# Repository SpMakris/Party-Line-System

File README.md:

# Party-Line-System
Party Line circuit implementation

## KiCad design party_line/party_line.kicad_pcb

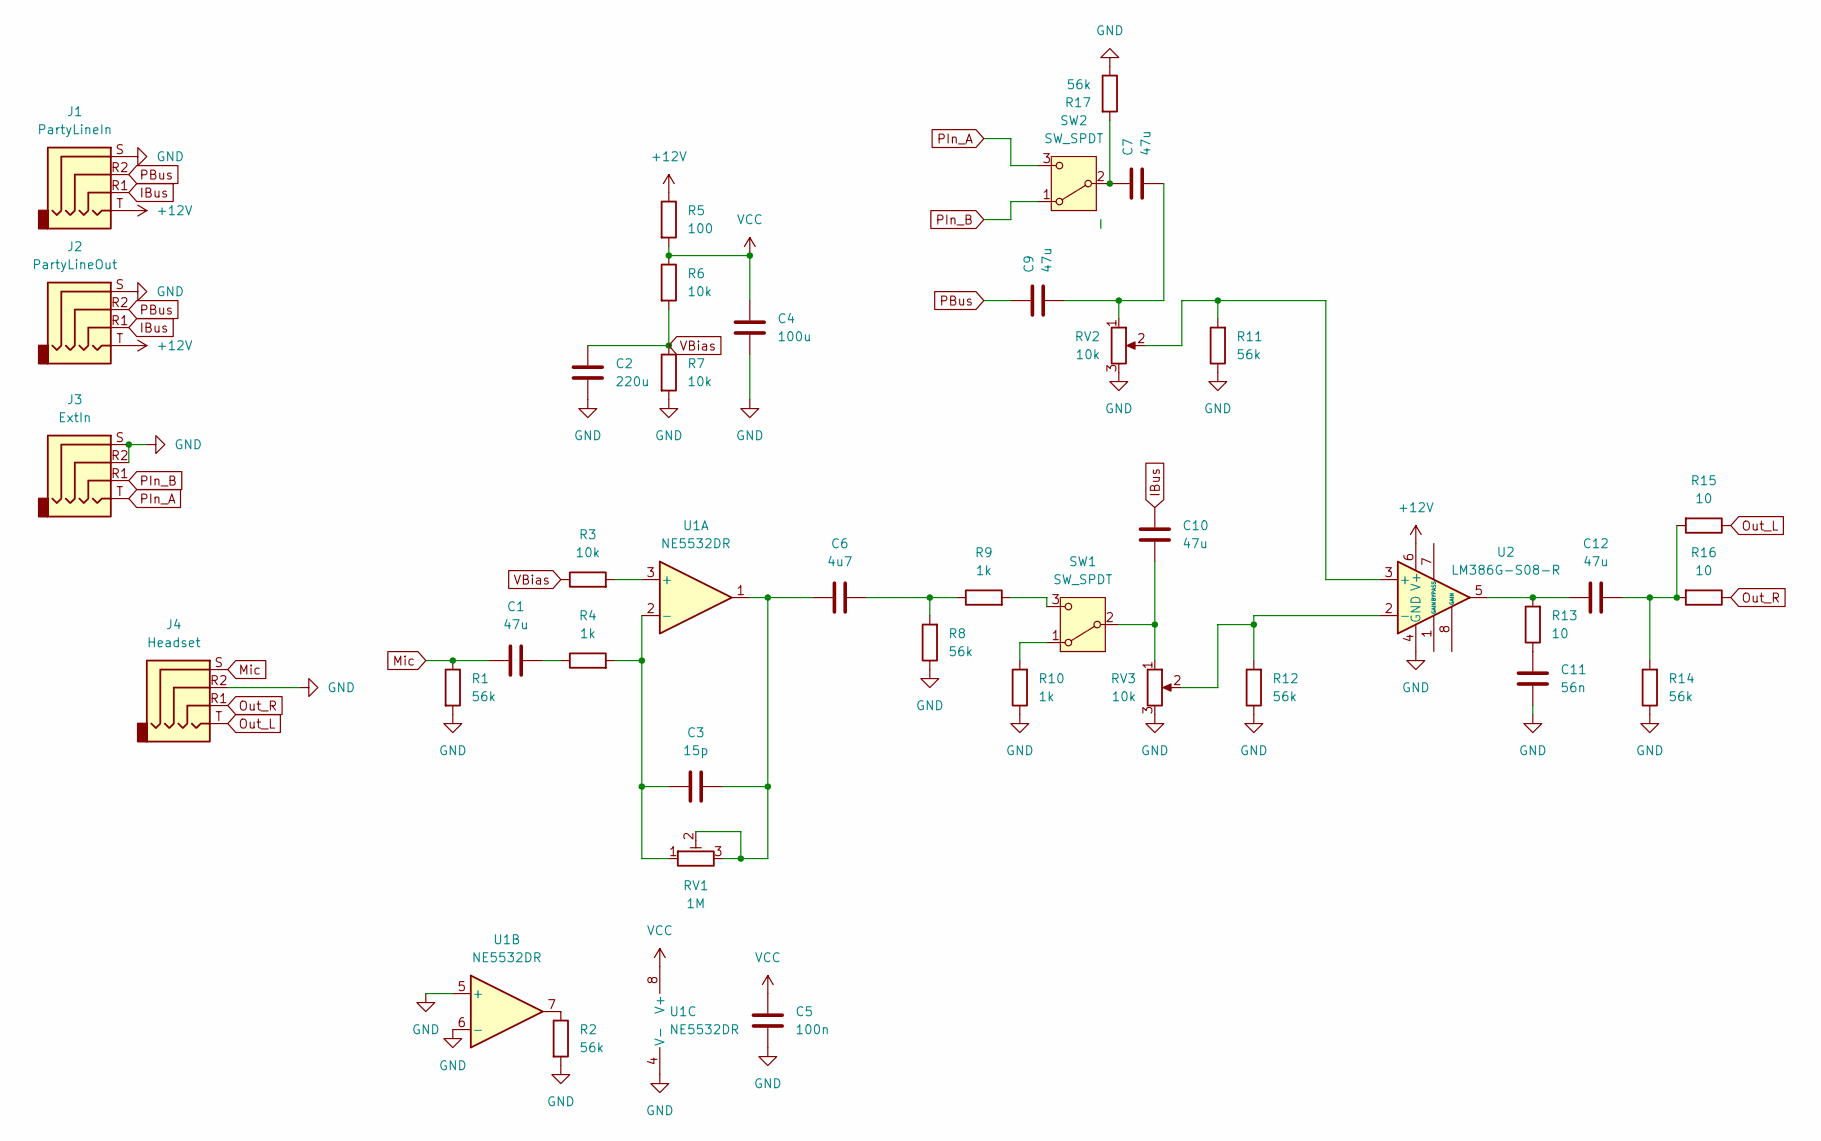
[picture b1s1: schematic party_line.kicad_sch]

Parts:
C1, C7, C9, C10, C12: 47u; C_Elec_6.3x5.4
C2: 220u; C_Elec_8x10.2
C3: 15p; C_0805_2012Metric_Pad1.18x1.45mm_HandSolder
C4: 100u; C_Elec_6.3x5.4
C5: 100n; C_0805_2012Metric_Pad1.18x1.45mm_HandSolder
C6: 4u7; C_1206_3216Metric_Pad1.33x1.80mm_HandSolder
C11: 56n; C_0805_2012Metric_Pad1.18x1.45mm_HandSolder
J1: PartyLineIn; PJ-320D
J2: PartyLineOut; PJ-320D
J3: ExtIn; PJ-320D; LCSC C431535
J4: Headset; PJ-320D
R1, R2, R8, R11, R12, R14, R17: 56k; R_0805_2012Metric_Pad1.20x1.40mm_HandSolder
R3, R6, R7: 10k; R_0805_2012Metric_Pad1.20x1.40mm_HandSolder
R4, R9, R10: 1k; R_0805_2012Metric_Pad1.20x1.40mm_HandSolder
R5: 100; R_0805_2012Metric_Pad1.20x1.40mm_HandSolder
R13, R15, R16: 10; R_0805_2012Metric_Pad1.20x1.40mm_HandSolder
RV1: 1M; 3314J-1
RV2, RV3: 10k; PinSocket_1x03_P2.54mm_Vertical
SW1, SW2: SW_SPDT; PinSocket_1x03_P2.54mm_Vertical
U1: NE5532DR; SOIC-8_3.9x4.9mm_P1.27mm
U2: LM386G-S08-R; SOP-8_3.9x4.9mm_P1.27mm

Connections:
+12V: J1.T, J2.T, R5.1, U2.6 (V+)
GND: C2.2, C4.2, C5.2, C11.2, J1.S, J2.S, J3.R2, J3.S, J4.R2, R1.2, R2.2, R7.2, R8.1, R10.1, R11.1, R12.1, R14.1, R17.1, RV2.3, RV3.3, U1.4 (V-), U1.5 (+), U1.6 (-), U2.4 (GND)
IBus: C10.1, J1.R1, J2.R1
Mic: C1.2, J4.S, R1.1
unnamed: C1.1, R4.1
unnamed: C3.2, C6.1, RV1.2, RV1.3, U1.1
unnamed: C6.2, R8.2, R9.1
unnamed: C7.2, C9.2, RV2.1
unnamed: C11.1, R13.1
unnamed: C12.1, R14.2, R15.2, R16.2
unnamed: C12.2, R13.2, U2.5
unnamed: R2.1, U1.7
unnamed: R10.2, SW1.1 (A)
unnamed: C10.2, RV3.1, SW1.2 (B)
unnamed: R9.2, SW1.3 (C)
unnamed: C7.1, R17.2, SW2.2 (B)
unnamed: R3.2, U1.3 (+)
unnamed: C3.1, R4.2, RV1.1, U1.2 (-)
unnamed: R11.2, RV2.2, U2.3 (+)
unnamed: R12.2, RV3.2, U2.2 (-)
Out_L: J4.T, R15.1
Out_R: J4.R1, R16.1
PBus: C9.1, J1.R2, J2.R2
PIn_A: J3.T, SW2.3 (C)
PIn_B: J3.R1, SW2.1 (A)
VBias: C2.1, R3.1, R6.2, R7.1
VCC: C4.1, C5.1, R5.2, R6.1, U1.8 (V+)

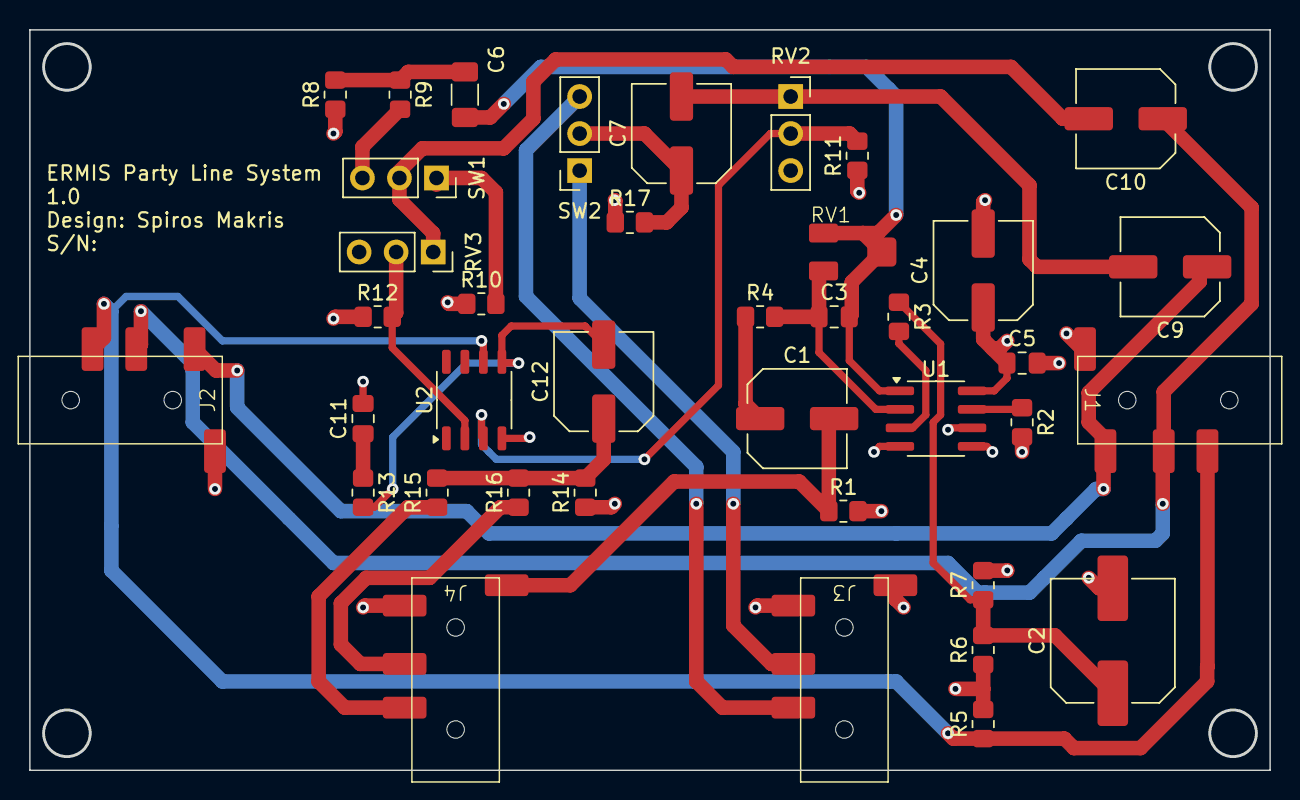
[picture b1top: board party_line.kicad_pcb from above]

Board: 4 copper layers, 85.0 x 50.7 mm, 39 parts (0 on the bottom side), 27 nets.

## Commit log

2025-12-23 layout
2025-12-24 reposition jacks
